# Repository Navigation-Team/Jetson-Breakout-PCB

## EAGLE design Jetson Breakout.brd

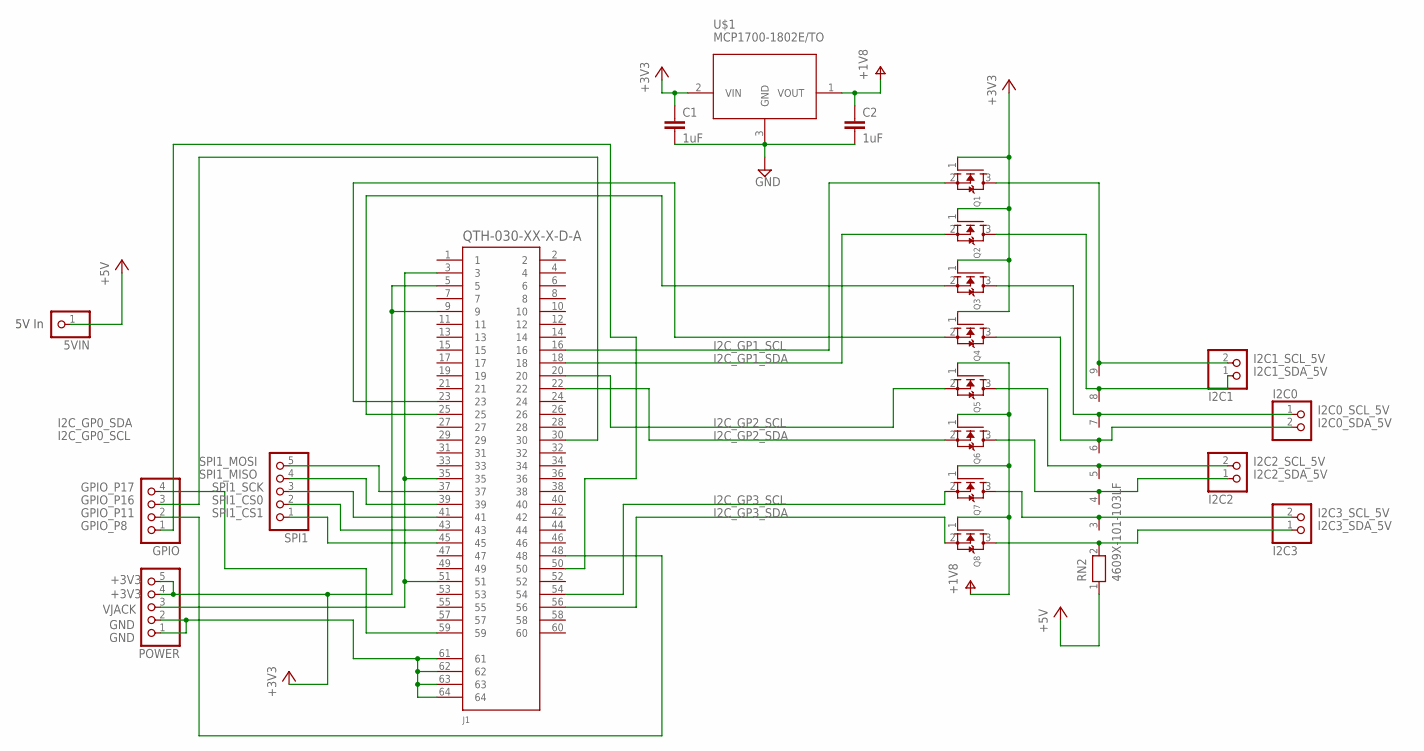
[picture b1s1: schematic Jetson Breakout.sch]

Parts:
5VIN: PINHD-1X1; 1X01
C1, C2: 1uF; C050-025X075
GPIO: PINHD-1X4; 1X04
I2C0, I2C1, I2C2, I2C3: PINHD-1X2; 1X02
J1: QTH-030-XX-X-D-A
POWER: PINHD-1X5; 1X05
Q1, Q2, Q3, Q4, Q5, Q6, Q7, Q8: MOSFET-NREFLOW; SOT23
RN2: 4609X-101-103LF; RN-9
SPI1: PINHD-1X5; 1X05
U$1: MCP1700-1802E/TO; TO92

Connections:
+1V8: C2.1, Q5.1 (G), Q6.1 (G), Q7.1 (G), Q8.1 (G), U$1.1 (VOUT)
+3V3: C1.1, J1.5, J1.9, POWER.4, POWER.5, Q1.1 (G), Q2.1 (G), Q3.1 (G), Q4.1 (G), U$1.2 (VIN)
+5V: 5VIN.1, RN2.1
GND: C1.2, C2.2, J1.61, J1.62, J1.63, J1.64, POWER.1, POWER.2, U$1.3 (GND)
GPIO_P8: GPIO.1, J1.50
GPIO_P11: GPIO.2, J1.48
GPIO_P16: GPIO.3, J1.30
GPIO_P17: GPIO.4, J1.59
I2C0_SCL_5V: I2C0.1, Q3.3 (D), RN2.7
I2C0_SDA_5V: I2C0.2, Q4.3 (D), RN2.6
I2C1_SCL_5V: I2C1.2, Q1.3 (D), RN2.9
I2C1_SDA_5V: I2C1.1, Q2.3 (D), RN2.8
I2C2_SCL_5V: I2C2.2, Q5.3 (D), RN2.5
I2C2_SDA_5V: I2C2.1, Q6.3 (D), RN2.4
I2C3_SCL_5V: I2C3.2, Q7.3 (D), RN2.3
I2C3_SDA_5V: I2C3.1, Q8.3 (D), RN2.2
I2C_GP0_SCL: J1.25, Q3.2 (S)
I2C_GP0_SDA: J1.23, Q4.2 (S)
I2C_GP1_SCL: J1.16, Q1.2 (S)
I2C_GP1_SDA: J1.18, Q2.2 (S)
I2C_GP2_SCL: J1.20, Q5.2 (S)
I2C_GP2_SDA: J1.22, Q6.2 (S)
I2C_GP3_SCL: J1.54, Q7.2 (S)
I2C_GP3_SDA: J1.56, Q8.2 (S)
SPI1_CS0: J1.43, SPI1.2
SPI1_CS1: J1.45, SPI1.1
SPI1_MISO: J1.39, SPI1.4
SPI1_MOSI: J1.37, SPI1.5
SPI1_SCK: J1.41, SPI1.3
VJACK: J1.3, J1.35, J1.51, POWER.3

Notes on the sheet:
5V In

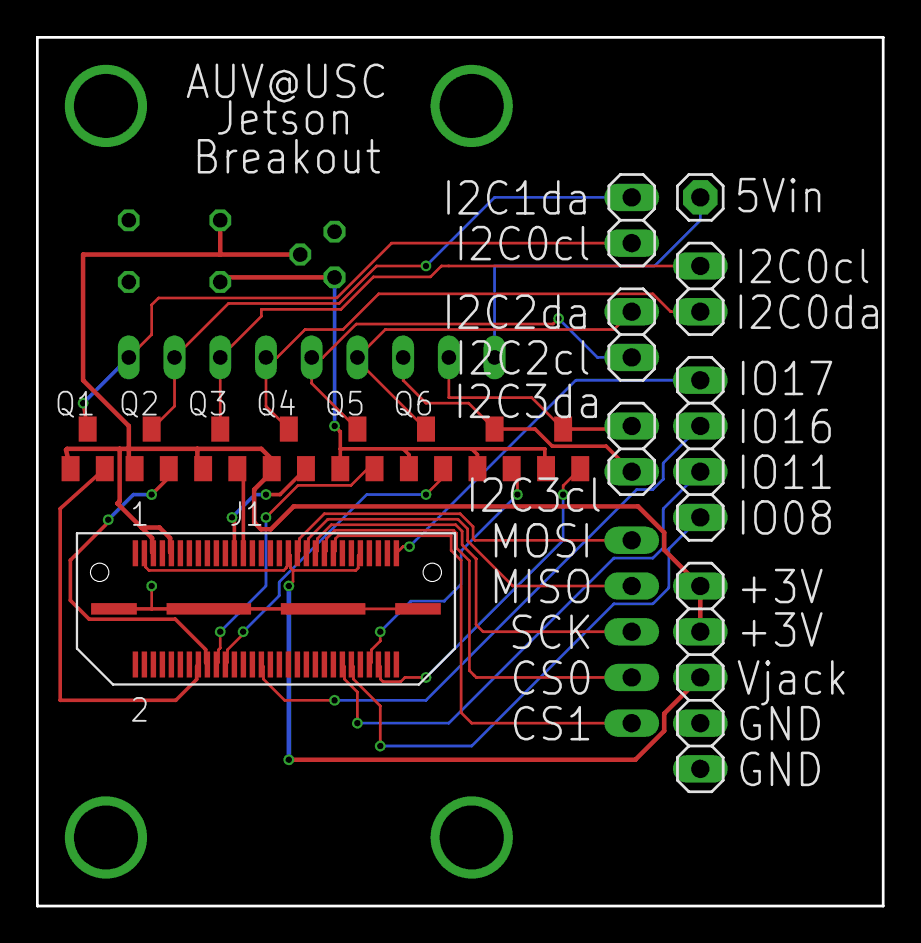
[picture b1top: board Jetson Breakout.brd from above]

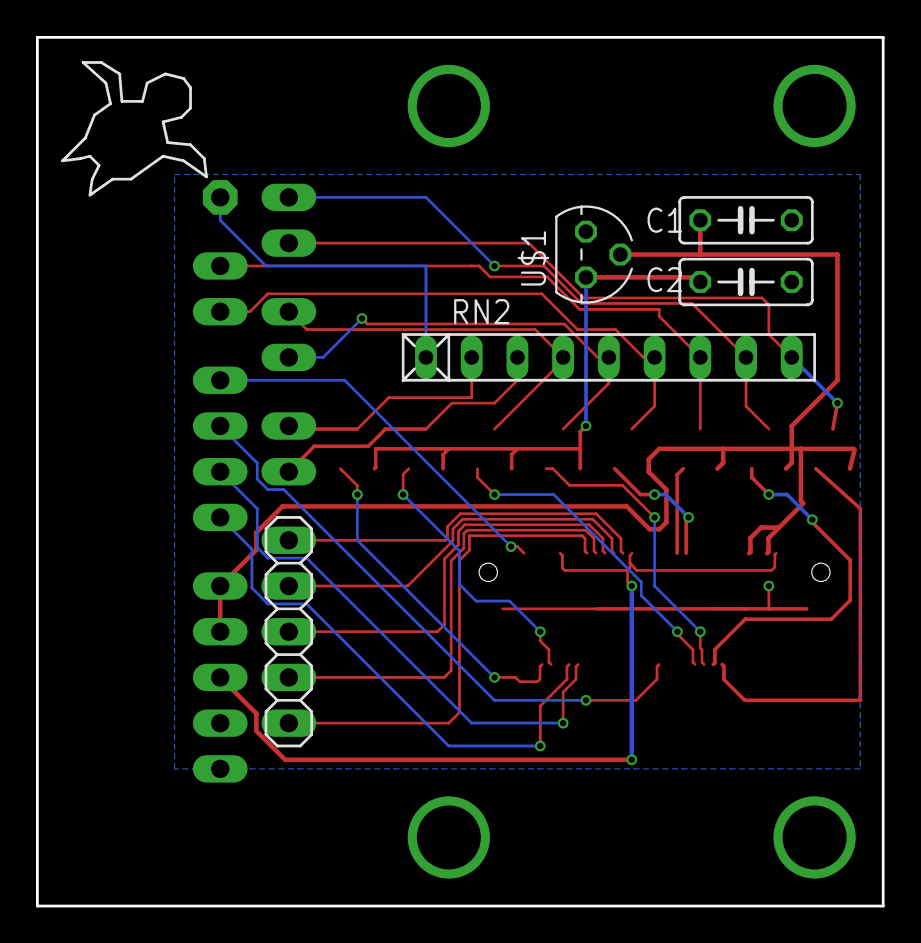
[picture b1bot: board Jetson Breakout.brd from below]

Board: 2 copper layers, 47.0 x 48.3 mm, 21 parts (5 on the bottom side), 30 nets.
